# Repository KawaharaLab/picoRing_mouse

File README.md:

# picoRing_mouse
pip install -r GUI/requirements.txt

python3 GUI/main.py -i GUI/setting/default.ini

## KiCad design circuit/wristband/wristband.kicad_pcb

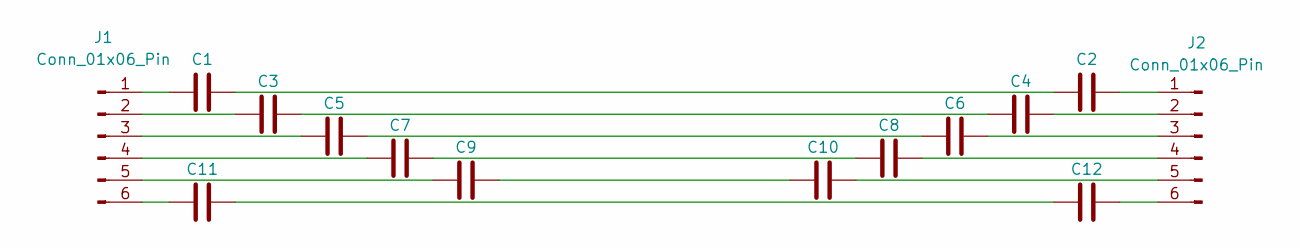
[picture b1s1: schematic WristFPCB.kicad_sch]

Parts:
C1, C2, C3, C4, C5, C6, C7, C8, C9, C10, C11, C12: C; C_0603_1608Metric
J1, J2: Conn_01x06_Pin; PinHeader_1x06_P2.00mm_Vertical

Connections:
unnamed: C1.2, C2.1
unnamed: C3.2, C4.1
unnamed: C5.2, C6.1
unnamed: C7.2, C8.1
unnamed: C9.2, C10.1
unnamed: C11.2, C12.1
unnamed: C1.1, J1.1
unnamed: C3.1, J1.2
unnamed: C5.1, J1.3
unnamed: C7.1, J1.4
unnamed: C9.1, J1.5
unnamed: C11.1, J1.6
unnamed: C2.2, J2.1
unnamed: C4.2, J2.2
unnamed: C6.2, J2.3
unnamed: C8.2, J2.4
unnamed: C10.2, J2.5
unnamed: C12.2, J2.6

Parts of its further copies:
C13, C14, C15, C16, C17, C18, C19, C20, C21, C22, C23, C24, C25, C26, C27, C28, C29, C30, C31, C32, C33, C34, C35, C36, C37, C38, C39, C40, C41, C42, C43, C44, C45, C46, C47, C48: C; C_0603_1608Metric
J3, J4, J5, J6, J7, J8: Conn_01x06_Pin; PinHeader_1x06_P2.00mm_Vertical

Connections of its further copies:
unnamed: C13.2, C23.1
unnamed: C14.2, C24.1
unnamed: C15.2, C22.1
unnamed: C16.2, C21.1
unnamed: C17.2, C20.1
unnamed: C18.2, C19.1
unnamed: C25.2, C35.1
unnamed: C26.2, C36.1
unnamed: C27.2, C34.1
unnamed: C28.2, C33.1
unnamed: C29.2, C32.1
unnamed: C30.2, C31.1
unnamed: C37.2, C47.1
unnamed: C38.2, C48.1
unnamed: C39.2, C46.1
unnamed: C40.2, C45.1
unnamed: C41.2, C44.1
unnamed: C42.2, C43.1
unnamed: C13.1, J3.1
unnamed: C15.1, J3.2
unnamed: C16.1, J3.3
unnamed: C17.1, J3.4
unnamed: C18.1, J3.5
unnamed: C14.1, J3.6
unnamed: C23.2, J4.1
unnamed: C22.2, J4.2
unnamed: C21.2, J4.3
unnamed: C20.2, J4.4
unnamed: C19.2, J4.5
unnamed: C24.2, J4.6
unnamed: C25.1, J5.1
unnamed: C27.1, J5.2
unnamed: C28.1, J5.3
unnamed: C29.1, J5.4
unnamed: C30.1, J5.5
unnamed: C26.1, J5.6
unnamed: C35.2, J6.1
unnamed: C34.2, J6.2
unnamed: C33.2, J6.3
unnamed: C32.2, J6.4
unnamed: C31.2, J6.5
unnamed: C36.2, J6.6
unnamed: C37.1, J7.1
unnamed: C39.1, J7.2
unnamed: C40.1, J7.3
unnamed: C41.1, J7.4
unnamed: C42.1, J7.5
unnamed: C38.1, J7.6
unnamed: C47.2, J8.1
unnamed: C46.2, J8.2
unnamed: C45.2, J8.3
unnamed: C44.2, J8.4
unnamed: C43.2, J8.5
unnamed: C48.2, J8.6

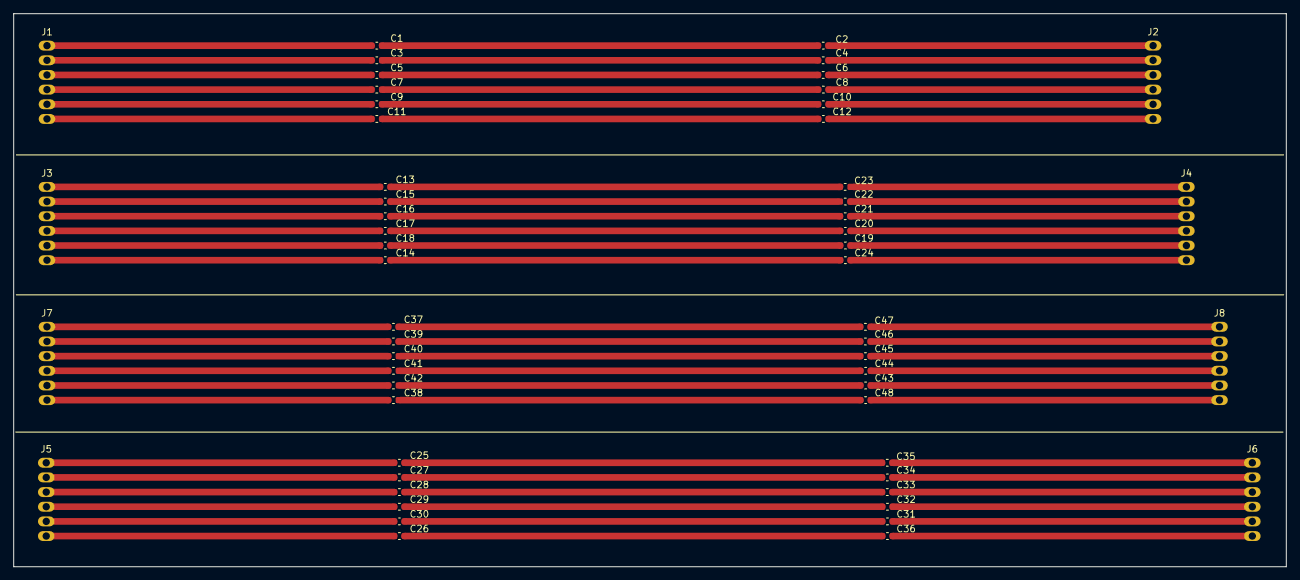
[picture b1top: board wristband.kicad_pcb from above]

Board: 2 copper layers, 191.0 x 83.0 mm, 56 parts (0 on the bottom side), 72 nets.

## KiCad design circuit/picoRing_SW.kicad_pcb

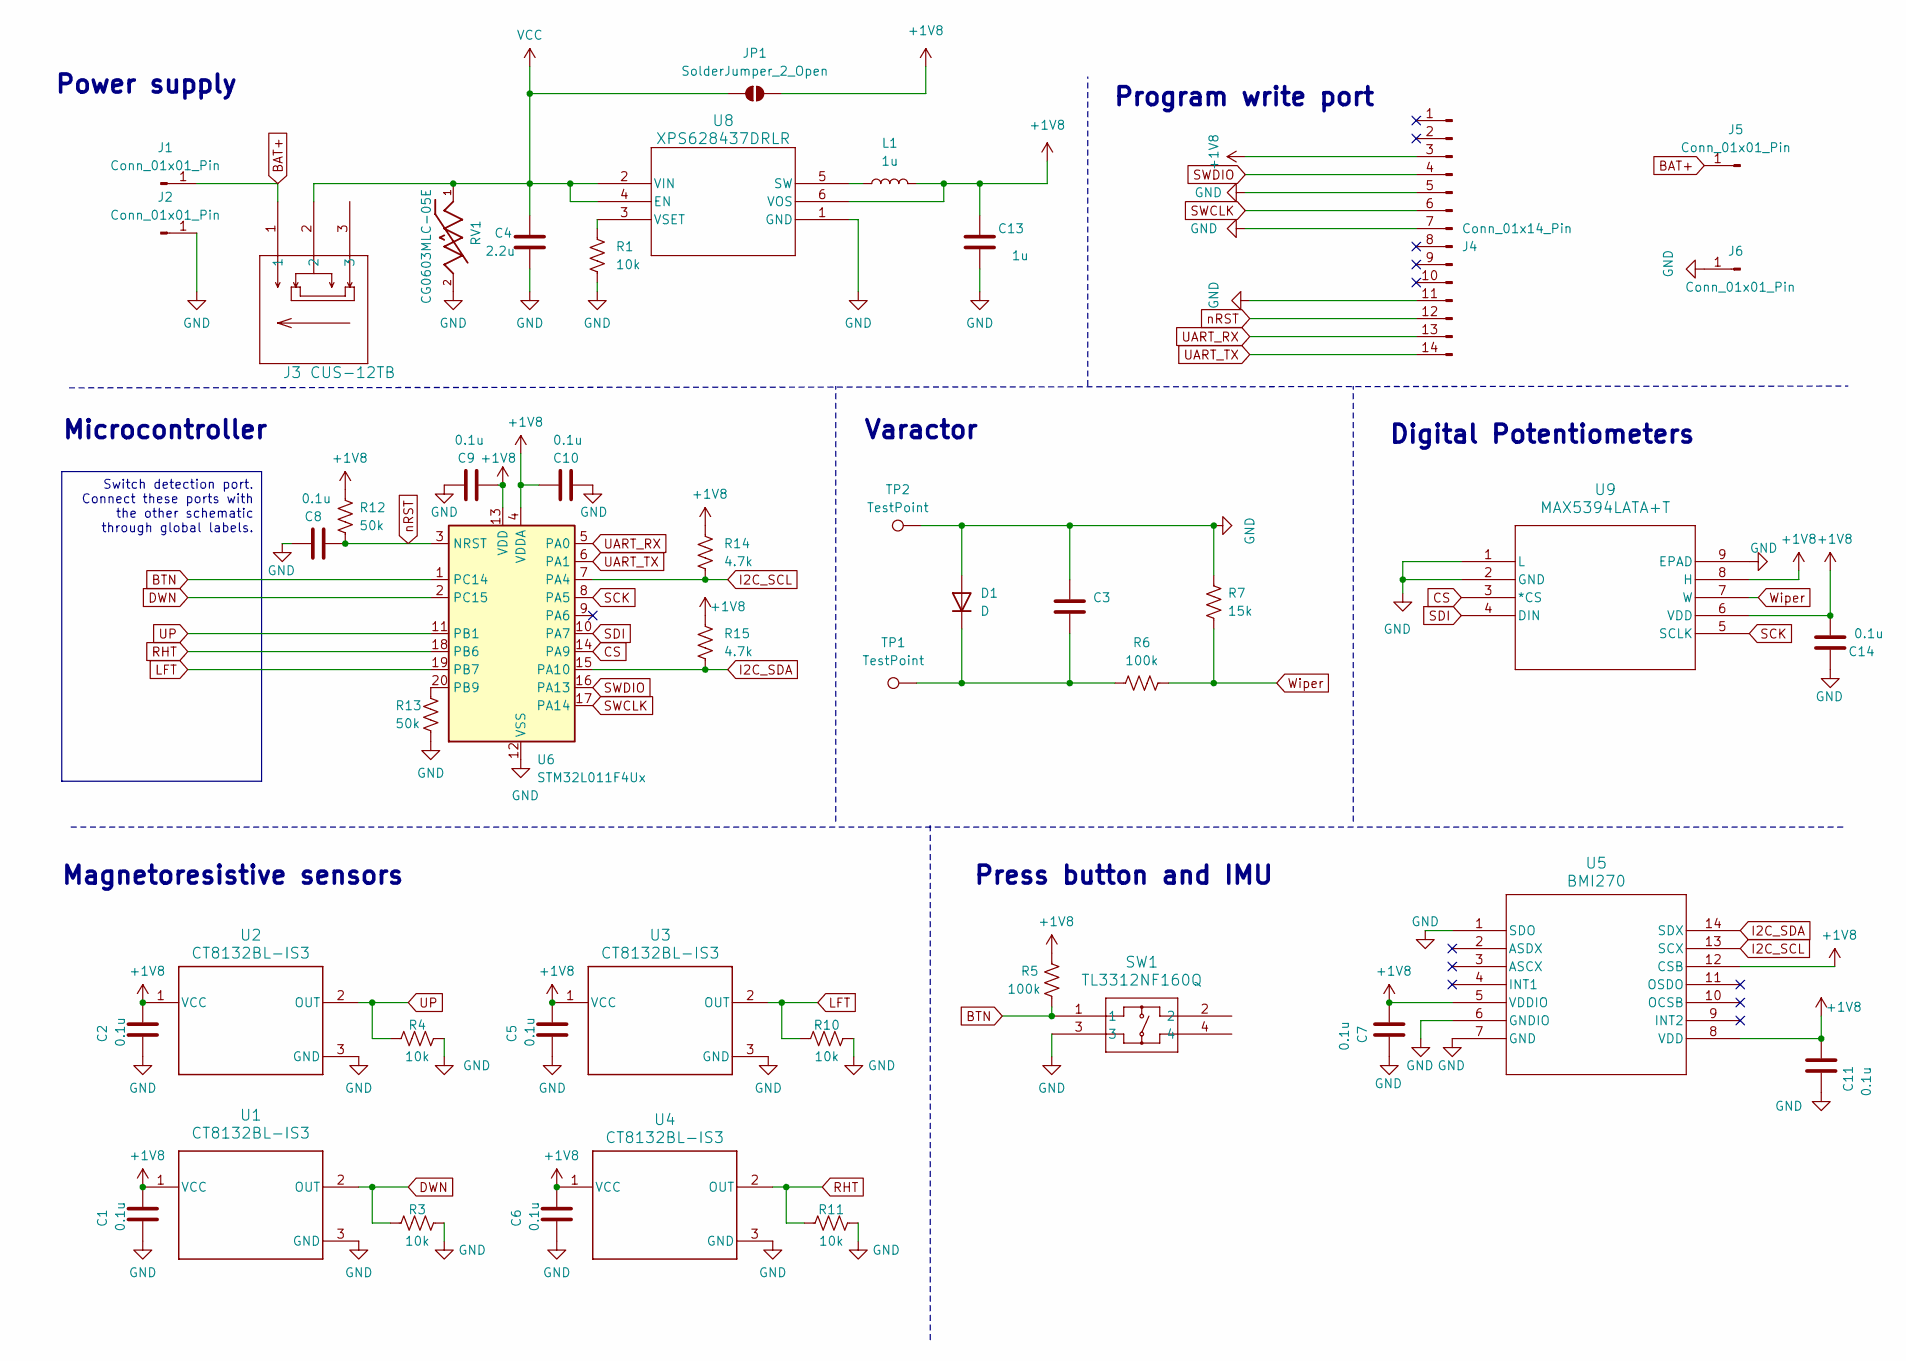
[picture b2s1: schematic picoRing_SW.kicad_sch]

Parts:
C1, C2, C5, C6, C7, C8, C9, C10, C11, C14: 0.1u; C_0402_1005Metric
C3: C; C_0402_1005Metric
C4: 2.2u; C_0402_1005Metric
C13: 1u; C_0402_1005Metric
D1: D; C_0402_1005Metric
J1, J2, J5, J6: Conn_01x01_Pin; padFront
J3: CUS-12TB; CUS-12TB_NDC
J4: Conn_01x14_Pin; Tag-Connect_TC2070-IDC-FP_2x07_P1.27mm_Vertical
JP1: SolderJumper_2_Open; SolderJumper-2_P1.3mm_Open_RoundedPad1.0x1.5mm
L1: 1u; L_0603_1608Metric
R1, R3, R4, R10, R11: 10k; R_0402_1005Metric
R5, R6: 100k; R_0402_1005Metric
R7: 15k; R_0402_1005Metric
R12, R13: 50k; R_0402_1005Metric
R14, R15: 4.7k; R_0402_1005Metric
RV1: CG0603MLC-05E; VARC1608X56N; PARTREV E
SW1: TL3312NF160Q; TL3312NF160Q_EWI
TP1, TP2: TestPoint; PinHeader_1x01_P1.27mm_Vertical
U1, U2, U3, U4: CT8132BL-IS3; DBZ0003A-IPC_C
U5: BMI270; BMI270_BOS
U6: STM32L011F4Ux; ST_UFQFPN-20_3x3mm_P0.5mm
U8: XPS628437DRLR; TPS628437DRLR_TEX
U9: MAX5394LATA+T; MAX5394

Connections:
+1V8: C1.2, C2.2, C5.2, C6.2, C7.1, C9.1, C10.1, C11.2, C13.1, C14.1, J4.3, JP1.2 (B), L1.2, R5.2, R12.2, R14.2, R15.2, U1.1 (VCC), U2.1 (VCC), U3.1 (VCC), U4.1 (VCC), U5.5 (VDDIO), U5.8 (VDD), U5.12 (CSB), U6.4 (VDDA), U6.13 (VDD), U8.6 (VOS), U9.6 (VDD), U9.8 (H)
BAT+: J1.1, J3.1, J5.1
BTN: R5.1, SW1.1, U6.1 (PC14)
CS: U6.14 (PA9), U9.3 (*CS)
DWN: R3.1, U1.2 (OUT), U6.2 (PC15)
GND: C1.1, C2.1, C3.2, C4.1, C5.1, C6.1, C7.2, C8.2, C9.2, C10.2, C11.1, C13.2, C14.2, D1.2 (A), J2.1, J4.5, J4.7, J4.11, J6.1, R1.1, R3.2, R4.2, R7.2, R10.2, R11.2, R13.1, RV1.2, SW1.3, TP2.1, U1.3 (GND), U2.3 (GND), U3.3 (GND), U4.3 (GND), U5.1 (SDO), U5.6 (GNDIO), U5.7 (GND), U6.12 (VSS), U8.1 (GND), U9.1 (L), U9.2 (GND), U9.9 (EPAD)
I2C_SCL: R14.1, U5.13 (SCX), U6.7 (PA4)
I2C_SDA: R15.1, U5.14 (SDX), U6.15 (PA10)
LFT: R10.1, U3.2 (OUT), U6.19 (PB7)
unnamed: C3.1, D1.1 (K), R6.2, TP1.1
unnamed: R13.2, U6.20 (PB9)
unnamed: L1.1, U8.5 (SW)
unnamed: R1.2, U8.3 (VSET)
RHT: R11.1, U4.2 (OUT), U6.18 (PB6)
SCK: U6.8 (PA5), U9.5 (SCLK)
SDI: U6.10 (PA7), U9.4 (DIN)
SWCLK: J4.6, U6.17 (PA14)
SWDIO: J4.4, U6.16 (PA13)
UART_RX: J4.13, U6.5 (PA0)
UART_TX: J4.14, U6.6 (PA1)
UP: R4.1, U2.2 (OUT), U6.11 (PB1)
VCC: C4.2, J3.2, JP1.1 (A), RV1.1, U8.2 (VIN), U8.4 (EN)
Wiper: R6.1, R7.1, U9.7 (W)
nRST: C8.1, J4.12, R12.1, U6.3 (NRST)

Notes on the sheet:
Switch detection port. Connect these ports with the other schematic through global labels.
Program write port
Press button and IMU
Microcontroller
Magnetoresistive sensors
Digital Potentiometers
Varactor
Power supply

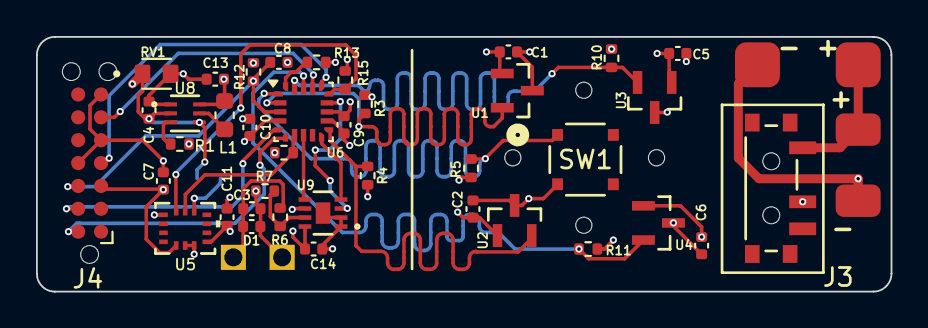
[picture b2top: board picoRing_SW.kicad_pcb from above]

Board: 4 copper layers, 47.5 x 14.1 mm, 46 parts (1 on the bottom side), 24 nets.

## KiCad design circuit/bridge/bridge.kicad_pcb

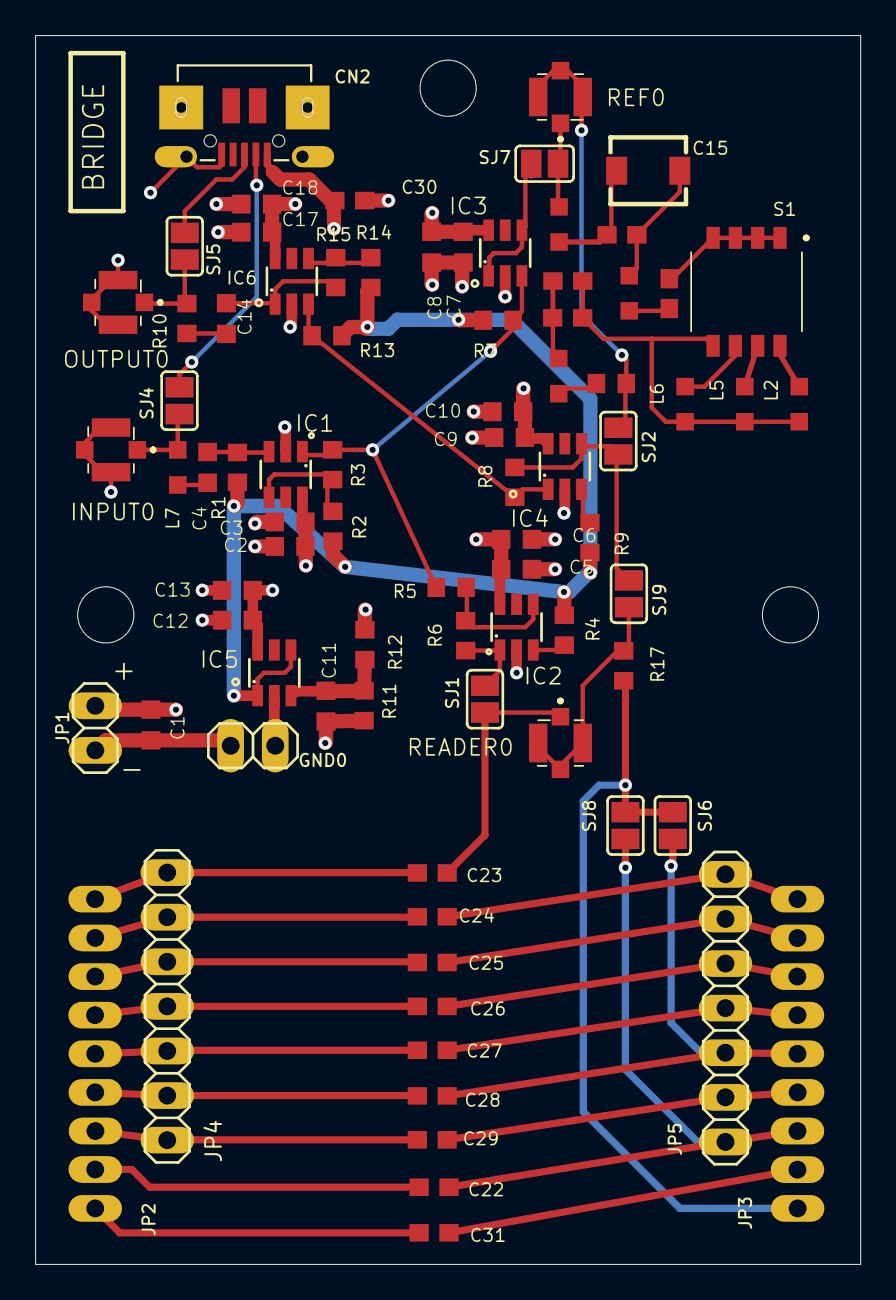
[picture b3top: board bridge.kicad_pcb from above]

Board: 4 copper layers, 47.0 x 70.0 mm, 84 parts (0 on the bottom side), 54 nets.

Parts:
@HOLE0, @HOLE1, @HOLE2: (no value)
C1: 10u; C0603K_334
C2, C5, C7, C9, C11, C12, C17: 0.1u; C0603K_334
C3, C6, C8, C10, C13, C18: 1.0u; C0603K_334
C4: 120p; C0603K_334
C14: C0603K_334
C15: CTRIMTZBX4_334
C16, C19, C20, C21, C22, C23, C24, C25, C26, C27, C28, C29, C30, C31: C1608_334
CN2: 4UCONN_20329
GND0: 1X02_325
IC1, IC2, IC3, IC4, IC5, IC6: LT6230CS6; TSOT23-6_261
INPUT0: 0734120114
JP1: 1X02_325
JP2, JP3: 1X09
JP4, JP5: 1X07_325
L1, L3, L4, L7: L2012C_334
L2: 0.2u; L2012C_334
L5: 0.15u; L2012C_334
L6: 0.1u; L2012C_334
OUTPUT0: 0734120114
R1, R4, R10: 50; R0603_334
R2, R3, R5, R6, R7, R8, R13, R14, R15: 100; R0603_334
R9: 0; R0603_334
R11, R12: 10k; R0603_334
R16, R17: R0603_334
READER0: 0734120114
REF0: 0734120114
S1: KAN1104RT
SJ1, SJ2, SJ4, SJ5, SJ6, SJ7, SJ8, SJ9: SJ_252

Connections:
GND: C1.2, C2.2, C3.2, C5.2, C6.2, C7.2, C8.2, C9.2, C10.2, C11.2, C12.2, C13.2, C17.2, C18.2, C30.2, CN2.BASE@1, CN2.BASE@2, CN2.GND, CN2.SPRT@1, CN2.SPRT@2, CN2.SPRT@3, CN2.SPRT@4, GND0.1, GND0.2, IC1.2, IC2.2, IC3.2, IC4.2, IC5.2, IC6.2, INPUT0.2, INPUT0.3, INPUT0.4, JP1.1, OUTPUT0.2, OUTPUT0.3, OUTPUT0.4, R11.1
unnamed: IC2.1, R6.1, SJ1.2
unnamed: C4.2, IC1.3, R1.2
unnamed: C22.1, JP2.2
unnamed: IC2.3, R4.1
unnamed: C14.2, R10.2
unnamed: IC4.3, R9.1
unnamed: IC1.1, IC3.3, R3.1, R5.2, R7.1
unnamed: L3.1, REF0.1, SJ7.2
unnamed: C16.2, L4.2
unnamed: C23.1, JP2.9, JP4.7
unnamed: IC2.4, R5.1, R6.2
unnamed: IC1.4, R2.2, R3.2
unnamed: INPUT0.1, L7.2, SJ4.2
unnamed: C11.1, IC5.3, R11.2, R12.1
unnamed: IC4.4, R8.2, SJ2.1, SJ9.2
unnamed: C14.1, IC6.1, R15.1
unnamed: IC4.1, IC6.3, R8.1, R13.1
unnamed: IC6.4, R14.2, R15.2
unnamed: IC3.1, IC3.4, SJ7.1
unnamed: CN2.D+, SJ5.1
unnamed: C15.2, C21.2, L3.2
unnamed: C15.1, C21.1, L4.1
unnamed: C16.1, S1.1, S1.2, S1.3, S1.4
unnamed: L1.1, R16.2
unnamed: OUTPUT0.1, R10.1, SJ5.2
unnamed: C24.2, JP3.1, JP5.1
unnamed: C24.1, JP2.8, JP4.6
unnamed: C25.2, JP3.2, JP5.2
unnamed: C25.1, JP2.7, JP4.5
unnamed: C26.2, JP3.3, JP5.3
unnamed: C26.1, JP2.6, JP4.4
unnamed: C27.2, JP3.4, JP5.4
unnamed: C27.1, JP2.5, JP4.3
unnamed: C28.1, JP2.4, JP4.2
unnamed: C28.2, JP3.5, JP5.5, SJ6.1
unnamed: C29.2, JP3.6, JP5.6
unnamed: C29.1, JP2.3, JP4.1
unnamed: R16.1, REF0.2, REF0.3, REF0.4, SJ2.2
unnamed: C4.1, L7.1
unnamed: CN2.D-, SJ4.1
unnamed: C23.2, READER0.1, SJ1.1
unnamed: JP3.9, R17.1, SJ6.2, SJ8.2
unnamed: C31.2, JP3.8
unnamed: C31.1, JP2.1
unnamed: C22.2, JP3.7, JP5.7, SJ8.1
unnamed: R17.2, READER0.2, READER0.3, READER0.4, SJ9.1
unnamed: L2.1, S1.8
unnamed: L5.1, S1.7
unnamed: L6.1, S1.6
unnamed: C19.2, C20.2, L2.2, L5.2, L6.2, S1.5
unnamed: C19.1, C20.1, L1.2
VCC: C1.1, C2.1, C3.1, C5.1, C6.1, C7.1, C8.1, C9.1, C10.1, C12.1, C13.1, C17.1, C18.1, C30.1, CN2.VBUS, IC1.6, IC2.6, IC3.6, IC4.6, IC5.6, IC6.6, JP1.2, R12.2
VCC/2: IC5.1, IC5.4, R1.1, R2.1, R4.2, R7.2, R9.2, R13.2, R14.1

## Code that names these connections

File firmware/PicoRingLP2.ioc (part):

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Mcu.Name=STM32L011F(3-4)Ux
Mcu.Package=UFQFPN20
Mcu.UserName=STM32L011F4Ux
PA0-CK_IN.Mode=Asynchronous
PA0-CK_IN.Signal=LPUART1_RX
PA1.Mode=Asynchronous
PA1.Signal=LPUART1_TX
PA10.Signal=I2C1_SDA
PA13.Mode=Serial_Wire
PA13.Signal=SYS_SWDIO
PA14.Mode=Serial_Wire
PA14.Signal=SYS_SWCLK
PA4.Signal=I2C1_SCL
PA5.Mode=TX_Only_Simplex_Unidirect_Master
PA5.Signal=SPI1_SCK
PA7.Mode=TX_Only_Simplex_Unidirect_Master
PA7.Signal=SPI1_MOSI
PA9.Signal=GPIO_Output
PB1.Signal=GPIO_Input
PB6.Signal=GPIO_Input
PB7.Signal=GPIO_Input
PC14-OSC32_IN.GPIOParameters=GPIO_ModeDefaultEXTI
PC14-OSC32_IN.GPIO_ModeDefaultEXTI=GPIO_MODE_IT_RISING
PC14-OSC32_IN.Signal=GPXTI14
PC15-OSC32_OUT.Signal=GPIO_Input
RCC.HSE_VALUE=8000000
RCC.SYSCLKFreq_VALUE=524288
board=custom

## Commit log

2025-06-24 init
2025-06-24 GUI_delete
2025-06-25 rename wristband
2025-06-25 add wristband
2025-06-25 Add .DS_Store to .gitignore
2025-11-21 switch to yamamoto
2025-11-21 Add installation and execution instructions
2025-11-21 Add instruction to run main.py with default settings
